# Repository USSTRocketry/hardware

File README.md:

USST Rocketry Avionics hardware

Telemetry board (Infozilla)

SRAD flight computer board (Phoenix)

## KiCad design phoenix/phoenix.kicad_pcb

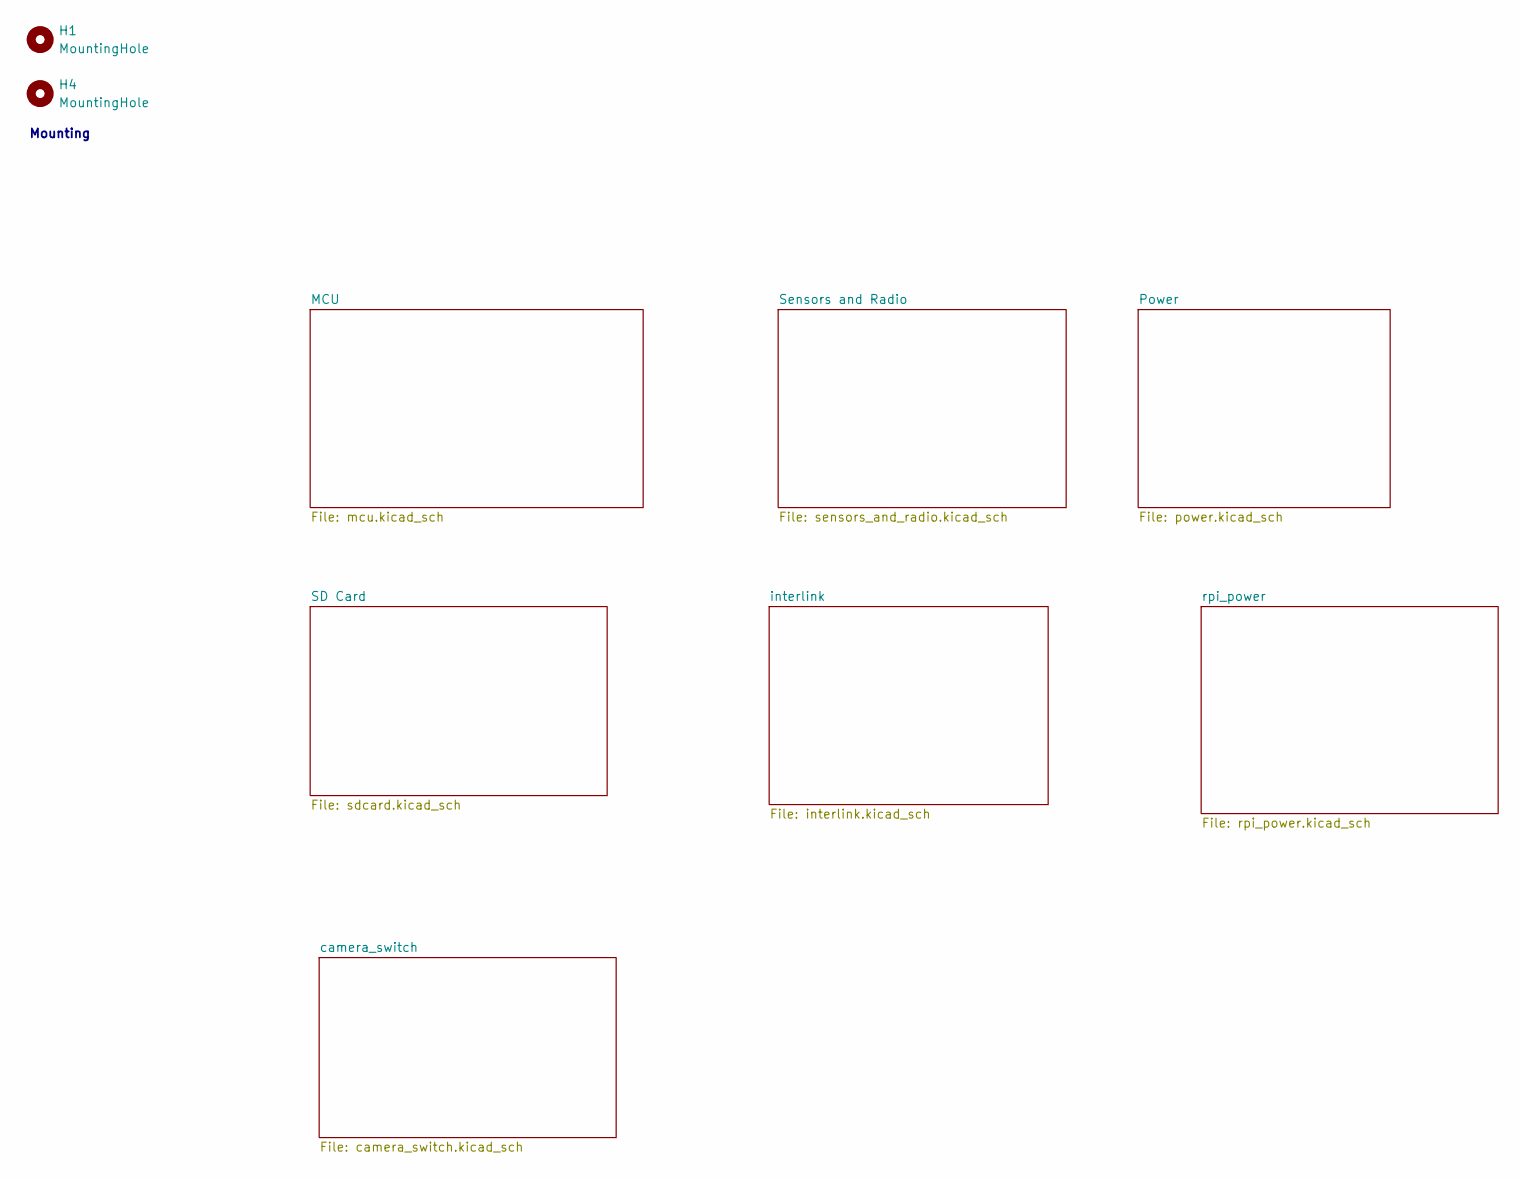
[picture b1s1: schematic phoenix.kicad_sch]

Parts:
H1, H4: MountingHole; MountingHole_3.2mm_M3

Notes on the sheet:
Mounting

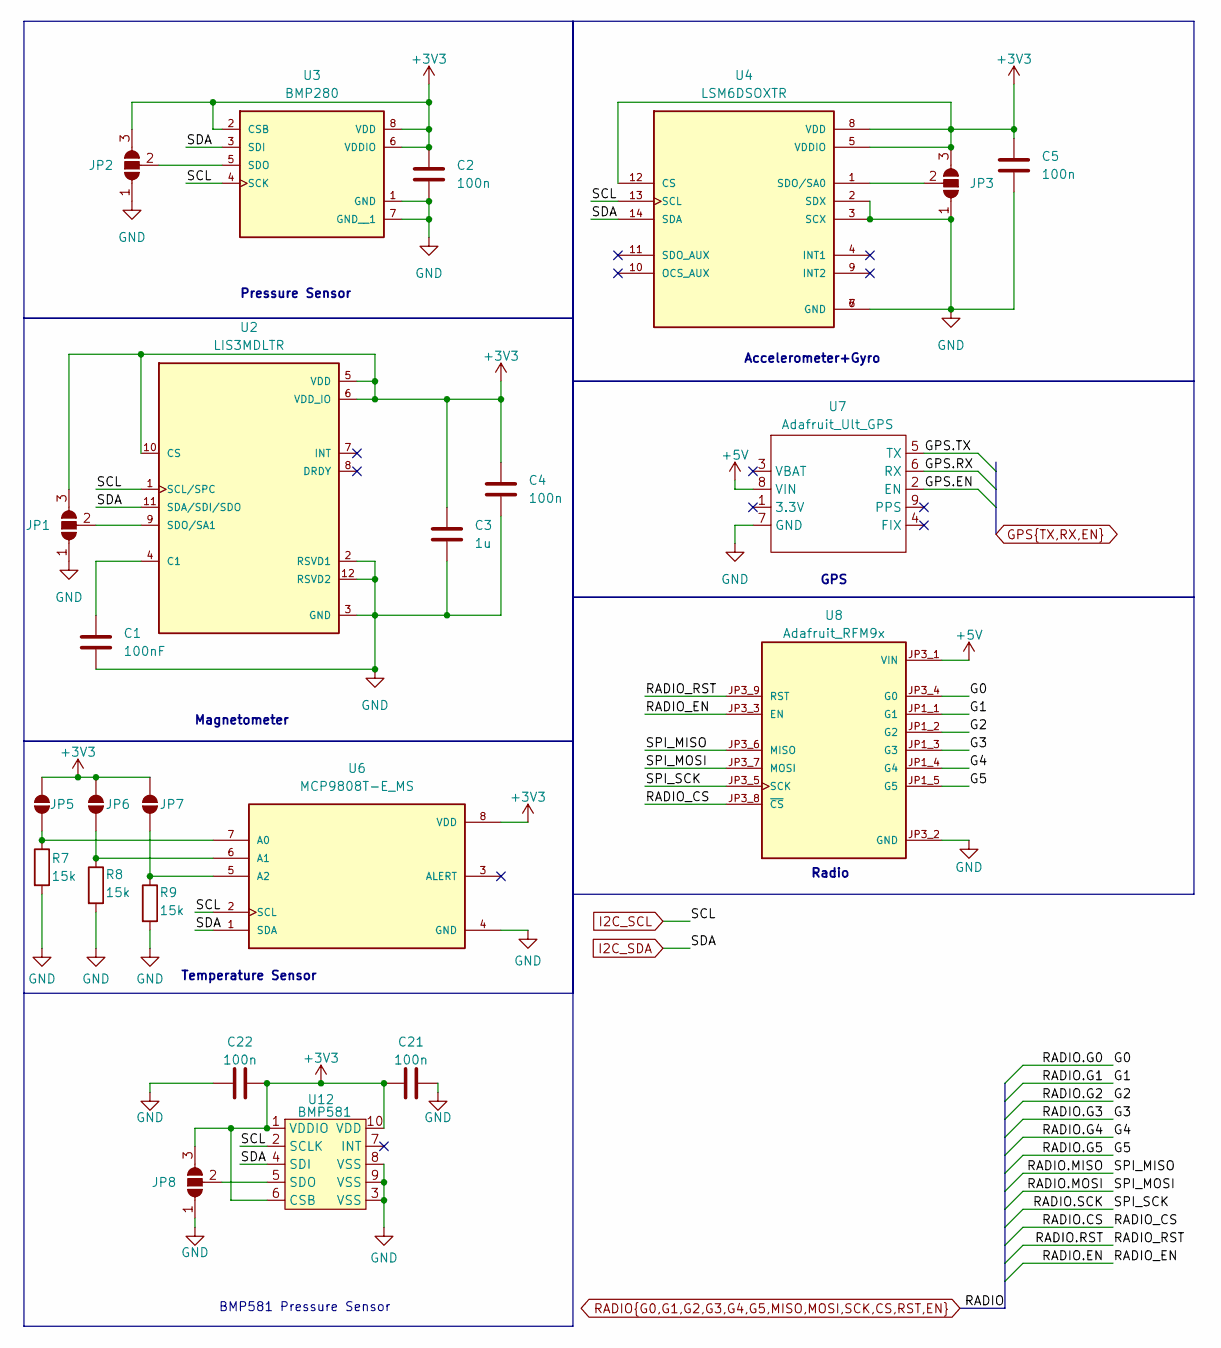
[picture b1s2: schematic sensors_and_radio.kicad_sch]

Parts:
C1: 100nF; C_0603_1608Metric_Pad1.08x0.95mm_HandSolder
C2, C4, C5, C21, C22: 100n; C_0603_1608Metric_Pad1.08x0.95mm_HandSolder
C3: 1u; C_0603_1608Metric_Pad1.08x0.95mm_HandSolder
JP1, JP2, JP3, JP8: SolderJumper_3_Open; SolderJumper-3_P1.3mm_Open_Pad1.0x1.5mm_NumberLabels
JP5, JP6, JP7: SolderJumper_2_Open; SolderJumper-2_P1.3mm_Open_Pad1.0x1.5mm
R7, R8, R9: 15k; R_0603_1608Metric_Pad0.98x0.95mm_HandSolder
U2: LIS3MDLTR; PARTREV 6
U3: BMP280; PART_REV 1.19
U4: LSM6DSOXTR; PARTREV 3.0
U6: MCP9808T-E_MS
U7: Adafruit_Ult_GPS
U8: Adafruit_RFM9x; Adafuit_RFM9x; PARTREV 2023-10-24
U12: BMP581; ST_HLGA-10_2x2mm_P0.5mm_LayoutBorder3x2y

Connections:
+3V3: C2.1, C3.1, C4.1, C5.2, C21.1, C22.2, JP1.3 (B), JP2.3 (B), JP3.3 (B), JP5.2 (B), JP6.2 (B), JP7.2 (B), JP8.3 (B), U2.5 (VDD), U2.6 (VDD_IO), U2.10 (CS), U3.2 (CSB), U3.6 (VDDIO), U3.8 (VDD), U4.5 (VDDIO), U4.8 (VDD), U4.12 (CS), U6.8 (VDD), U12.1 (VDDIO), U12.6 (CSB), U12.10 (VDD); also elsewhere on the board
+5V: U7.8 (VIN), U8.JP3_1 (VIN); also elsewhere on the board
GND: C1.2, C2.2, C3.2, C4.2, C5.1, C21.2, C22.1, JP1.1 (A), JP2.1 (A), JP3.1 (A), JP8.1 (A), R7.2, R8.2, R9.2, U2.2 (RSVD1), U2.3 (GND), U2.12 (RSVD2), U3.1 (GND), U3.7 (GND__1), U4.2 (SDX), U4.3 (SCX), U4.6 (GND), U4.7 (GND), U6.4 (GND), U7.7 (GND), U8.JP3_2 (GND), U12.3 (VSS), U12.8 (VSS), U12.9 (VSS); also elsewhere on the board
GPS.EN: U7.2 (EN); also elsewhere on the board
GPS.RX: U7.6 (RX); also elsewhere on the board
GPS.TX: U7.5 (TX); also elsewhere on the board
I2C_SCL: U2.1 (SCL/SPC), U3.4 (SCK), U4.13 (SCL), U6.2 (SCL), U12.2 (SCLK); also elsewhere on the board
I2C_SDA: U2.11 (SDA/SDI/SDO), U3.3 (SDI), U4.14 (SDA), U6.1 (SDA), U12.4 (SDI); also elsewhere on the board
unnamed: JP1.2 (C), U2.9 (SDO/SA1)
unnamed: JP2.2 (C), U3.5 (SDO)
unnamed: JP3.2 (C), U4.1 (SDO/SA0)
unnamed: JP5.1 (A), R7.1, U6.7 (A0)
unnamed: JP6.1 (A), R8.1, U6.6 (A1)
unnamed: JP7.1 (A), R9.1, U6.5 (A2)
unnamed: JP8.2 (C), U12.5 (SDO)
unnamed: C1.1, U2.4 (C1)
RADIO.CS: U8.JP3_8 (~CS); also elsewhere on the board
RADIO.EN: U8.JP3_3 (EN); also elsewhere on the board
RADIO.G0: U8.JP3_4 (G0); also elsewhere on the board
RADIO.G1: U8.JP1_1 (G1); also elsewhere on the board
RADIO.G2: U8.JP1_2 (G2); also elsewhere on the board
RADIO.G3: U8.JP1_3 (G3); also elsewhere on the board
RADIO.G4: U8.JP1_4 (G4); also elsewhere on the board
RADIO.G5: U8.JP1_5 (G5); also elsewhere on the board
RADIO.MISO: U8.JP3_6 (MISO); also elsewhere on the board
RADIO.MOSI: U8.JP3_7 (MOSI); also elsewhere on the board
RADIO.RST: U8.JP3_9 (RST); also elsewhere on the board
RADIO.SCK: U8.JP3_5 (SCK); also elsewhere on the board

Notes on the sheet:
Radio
Magnetometer
Temperature Sensor
Pressure Sensor
Accelerometer+Gyro
GPS
BMP581 Pressure Sensor

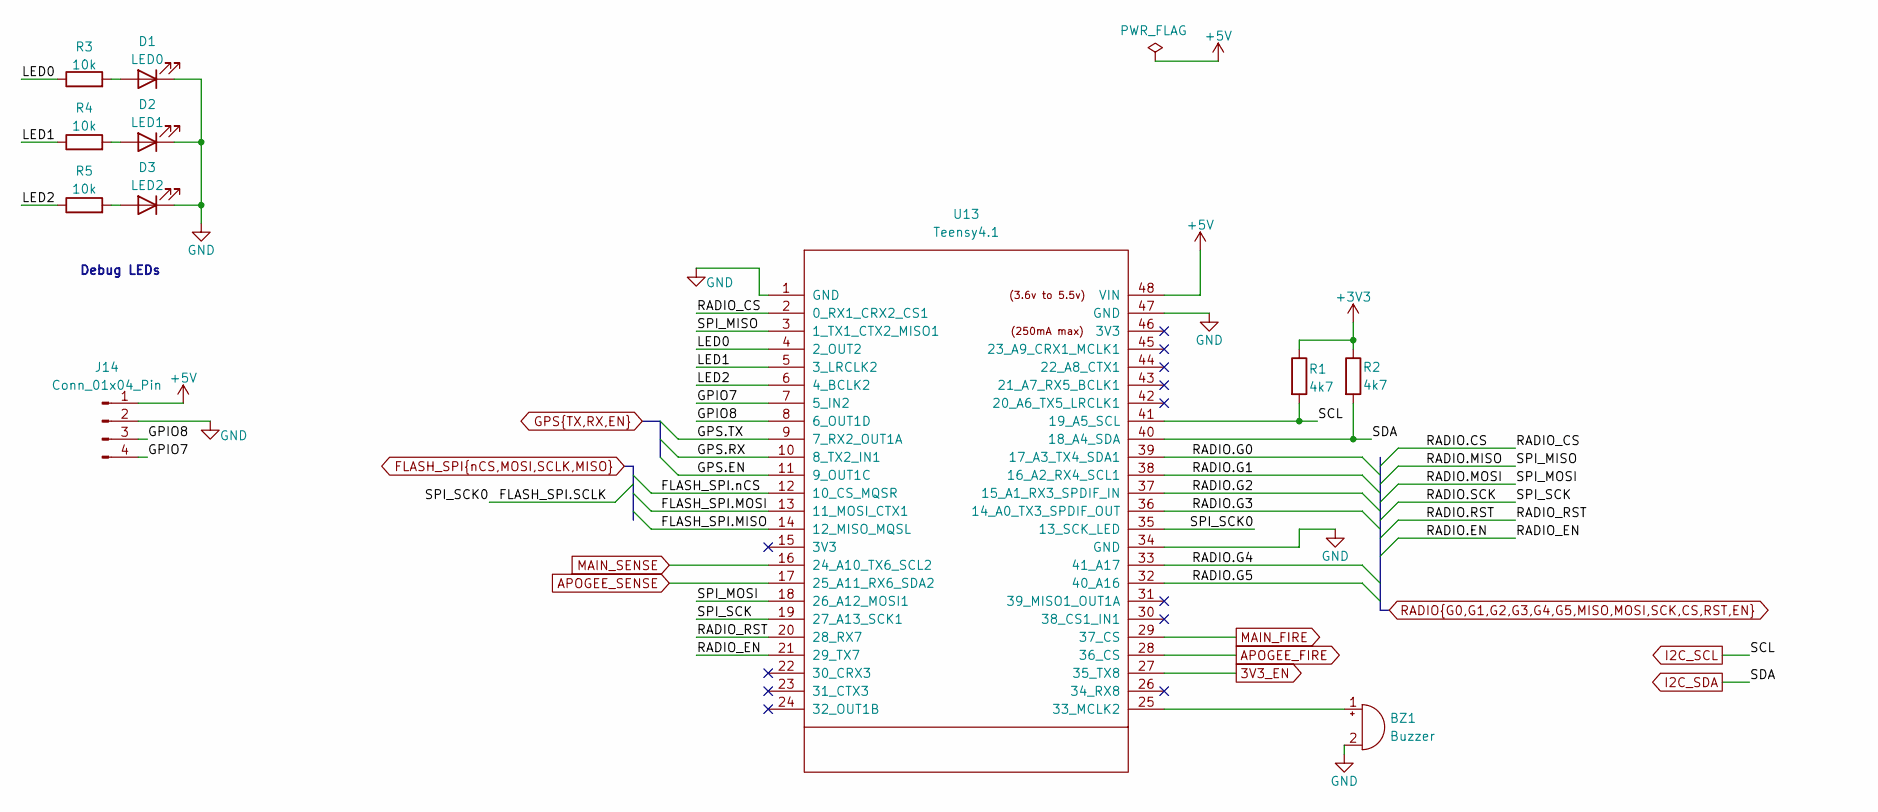
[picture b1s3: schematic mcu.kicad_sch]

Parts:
BZ1: Buzzer; MagneticBuzzer_PUI_AT-0927-TT-6-R
D1: LED0; LED_0603_1608Metric
D2: LED1; LED_0603_1608Metric
D3: LED2; LED_0603_1608Metric
J14: Conn_01x04_Pin; JST_XH_S4B-XH-A_1x04_P2.50mm_Horizontal
R1, R2: 4k7; R_0603_1608Metric_Pad0.98x0.95mm_HandSolder
R3, R4, R5: 10k; R_0603_1608Metric_Pad0.98x0.95mm_HandSolder
U13: Teensy4.1; Teensy41_simplified

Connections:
3V3_EN: U13.27 (35_TX8); also elsewhere on the board
+3V3: R1.1, R2.1; also elsewhere on the board
+5V: J14.1, U13.48 (VIN); also elsewhere on the board
/MCU/GPIO7: J14.4, U13.7 (5_IN2)
/MCU/GPIO8: J14.3, U13.8 (6_OUT1D)
/MCU/LED0: R3.1, U13.4 (2_OUT2)
/MCU/LED1: R4.1, U13.5 (3_LRCLK2)
/MCU/LED2: R5.1, U13.6 (4_BCLK2)
APOGEE_FIRE: U13.28 (36_CS); also elsewhere on the board
APOGEE_SENSE: U13.17 (25_A11_RX6_SDA2); also elsewhere on the board
FLASH_SPI.MISO: U13.14 (12_MISO_MQSL); also elsewhere on the board
FLASH_SPI.MOSI: U13.13 (11_MOSI_CTX1); also elsewhere on the board
FLASH_SPI.SCLK: U13.35 (13_SCK_LED); also elsewhere on the board
FLASH_SPI.nCS: U13.12 (10_CS_MQSR); also elsewhere on the board
GND: BZ1.2 (-), D1.1 (K), D2.1 (K), D3.1 (K), J14.2, U13.1 (GND), U13.34 (GND), U13.47 (GND); also elsewhere on the board
GPS.EN: U13.11 (9_OUT1C); also elsewhere on the board
GPS.RX: U13.10 (8_TX2_IN1); also elsewhere on the board
GPS.TX: U13.9 (7_RX2_OUT1A); also elsewhere on the board
I2C_SCL: R1.2, U13.41 (19_A5_SCL); also elsewhere on the board
I2C_SDA: R2.2, U13.40 (18_A4_SDA); also elsewhere on the board
MAIN_FIRE: U13.29 (37_CS); also elsewhere on the board
MAIN_SENSE: U13.16 (24_A10_TX6_SCL2); also elsewhere on the board
unnamed: BZ1.1 (+), U13.25 (33_MCLK2)
unnamed: D1.2 (A), R3.2
unnamed: D2.2 (A), R4.2
unnamed: D3.2 (A), R5.2
RADIO.CS: U13.2 (0_RX1_CRX2_CS1); also elsewhere on the board
RADIO.EN: U13.21 (29_TX7); also elsewhere on the board
RADIO.G0: U13.39 (17_A3_TX4_SDA1); also elsewhere on the board
RADIO.G1: U13.38 (16_A2_RX4_SCL1); also elsewhere on the board
RADIO.G2: U13.37 (15_A1_RX3_SPDIF_IN); also elsewhere on the board
RADIO.G3: U13.36 (14_A0_TX3_SPDIF_OUT); also elsewhere on the board
RADIO.G4: U13.33 (41_A17); also elsewhere on the board
RADIO.G5: U13.32 (40_A16); also elsewhere on the board
RADIO.MISO: U13.3 (1_TX1_CTX2_MISO1); also elsewhere on the board
RADIO.MOSI: U13.18 (26_A12_MOSI1); also elsewhere on the board
RADIO.RST: U13.20 (28_RX7); also elsewhere on the board
RADIO.SCK: U13.19 (27_A13_SCK1); also elsewhere on the board

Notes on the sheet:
Debug LEDs

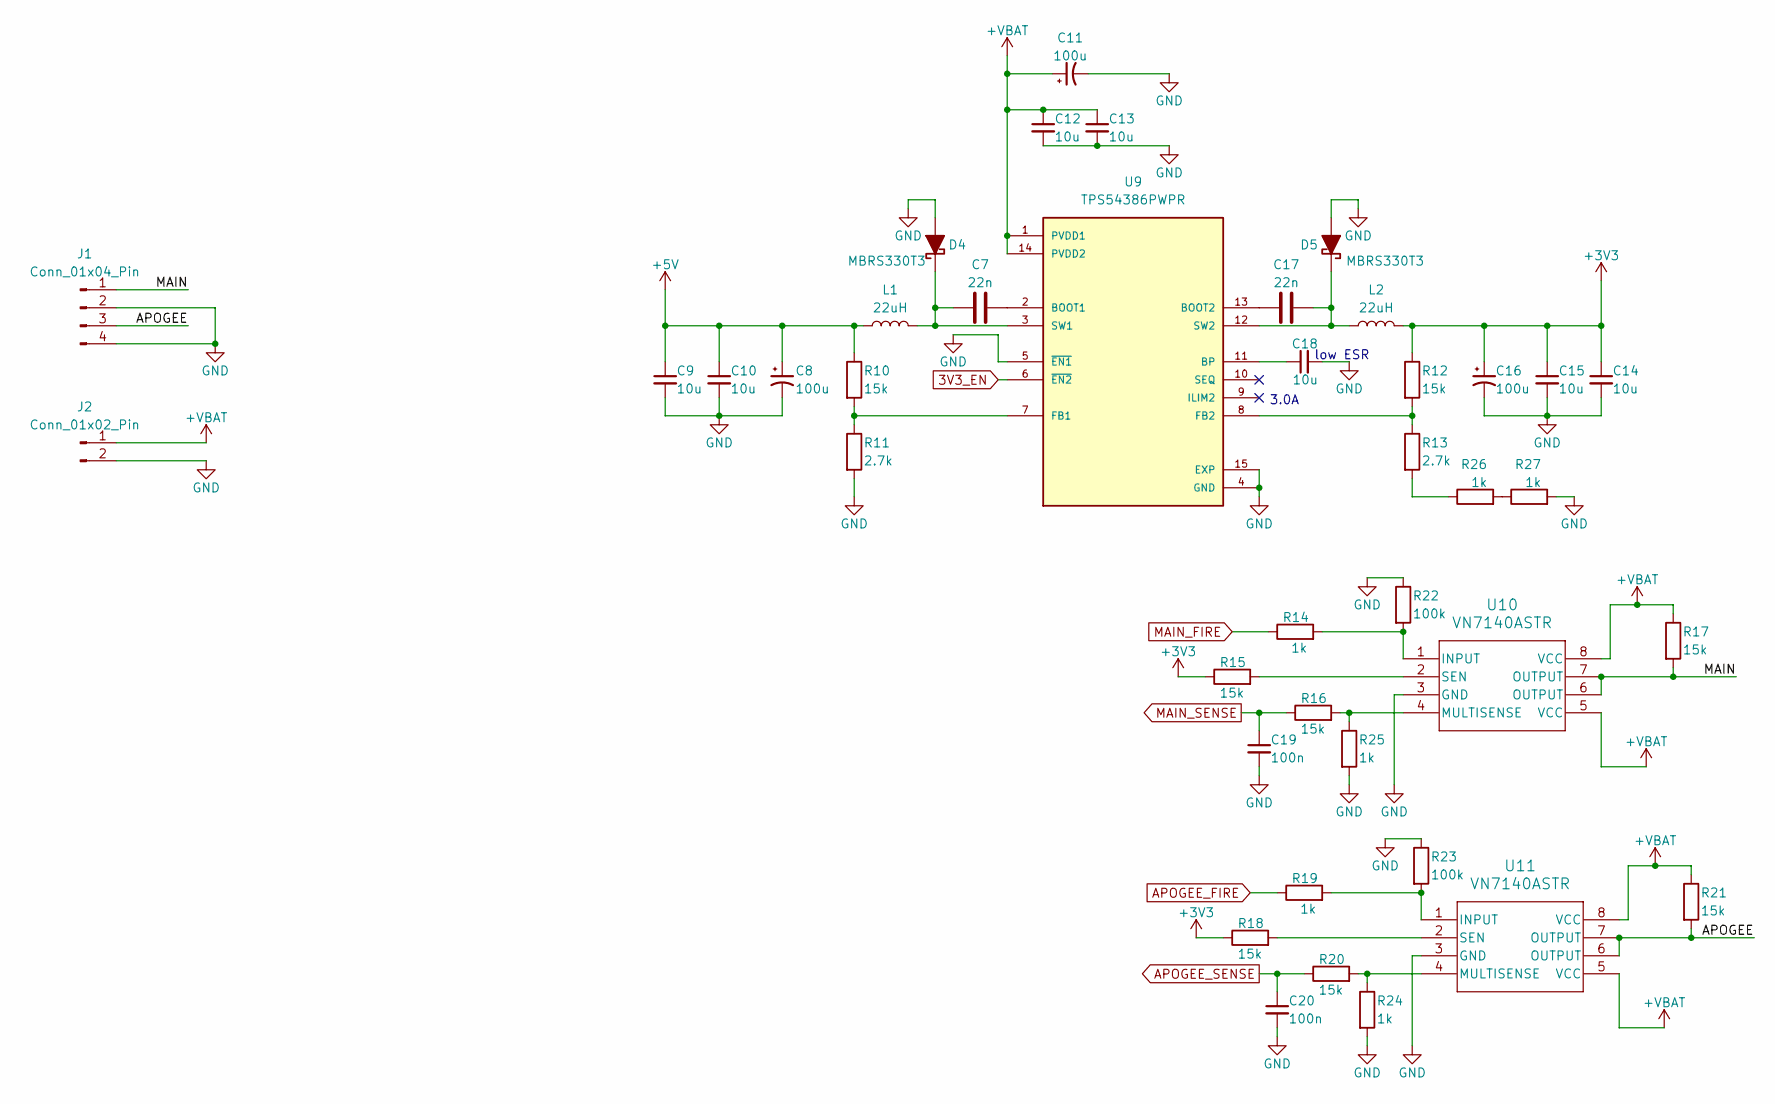
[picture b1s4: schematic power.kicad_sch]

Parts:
C7, C17: 22n; C_0603_1608Metric_Pad1.08x0.95mm_HandSolder
C8, C11, C16: 100u; C_0603_1608Metric_Pad1.08x0.95mm_HandSolder
C9, C10, C12, C13, C14, C15, C18: 10u; C_0603_1608Metric_Pad1.08x0.95mm_HandSolder
C19, C20: 100n; C_0603_1608Metric_Pad1.08x0.95mm_HandSolder
D4, D5: MBRS330T3; D_SMB_Handsoldering
J1: Conn_01x04_Pin; JST_XH_S4B-XH-A_1x04_P2.50mm_Horizontal
J2: Conn_01x02_Pin; JST_XH_S2B-XH-A_1x02_P2.50mm_Horizontal
L1, L2: 22uH; L_AMDLH5030S
R10, R12, R15, R16, R17, R18, R20, R21: 15k; R_0603_1608Metric_Pad0.98x0.95mm_HandSolder
R11, R13: 2.7k; R_0603_1608Metric_Pad0.98x0.95mm_HandSolder
R14, R19, R24, R25, R26, R27: 1k; R_0603_1608Metric_Pad0.98x0.95mm_HandSolder
R22, R23: 100k; R_0603_1608Metric_Pad0.98x0.95mm_HandSolder
U9: TPS54386PWPR; IC_TPS54386PWPR; PARTREV C
U10, U11: VN7140ASTR; VN7140ASTR_SO-8

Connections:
3V3_EN: U9.6 (~EN2); also elsewhere on the board
+3V3: C14.1, C15.1, C16.1, L2.1, R12.1, R15.1, R18.1; also elsewhere on the board
+5V: C8.1, C9.1, C10.1, L1.1, R10.1; also elsewhere on the board
+VBAT: C11.1, C12.1, C13.1, J2.1, R17.1, R21.1, U9.1 (PVDD1), U9.14 (PVDD2), U10.5 (VCC), U10.8 (VCC), U11.5 (VCC), U11.8 (VCC)
/Power/APOGEE: J1.3, R21.2, U11.6 (OUTPUT), U11.7 (OUTPUT)
/Power/MAIN: J1.1, R17.2, U10.6 (OUTPUT), U10.7 (OUTPUT)
APOGEE_FIRE: R19.1; also elsewhere on the board
APOGEE_SENSE: C20.1, R20.1; also elsewhere on the board
GND: C8.2, C9.2, C10.2, C11.2, C12.2, C13.2, C14.2, C15.2, C16.2, C18.2, C19.2, C20.2, D4.2 (A), D5.2 (A), J1.2, J1.4, J2.2, R11.2, R22.1, R23.1, R24.2, R25.2, R27.2, U9.4 (GND), U9.5 (~EN1), U9.15 (EXP), U10.3 (GND), U11.3 (GND); also elsewhere on the board
MAIN_FIRE: R14.1; also elsewhere on the board
MAIN_SENSE: C19.1, R16.1; also elsewhere on the board
unnamed: C7.1, D4.1 (K), L1.2, U9.3 (SW1)
unnamed: C17.1, D5.1 (K), L2.2, U9.12 (SW2)
unnamed: R13.2, R26.1
unnamed: R26.2, R27.1
unnamed: C7.2, U9.2 (BOOT1)
unnamed: C17.2, U9.13 (BOOT2)
unnamed: C18.1, U9.11 (BP)
unnamed: R10.2, R11.1, U9.7 (FB1)
unnamed: R12.2, R13.1, U9.8 (FB2)
unnamed: R14.2, R22.2, U10.1 (INPUT)
unnamed: R16.2, R25.1, U10.4 (MULTISENSE)
unnamed: R15.2, U10.2 (SEN)
unnamed: R19.2, R23.2, U11.1 (INPUT)
unnamed: R20.2, R24.1, U11.4 (MULTISENSE)
unnamed: R18.2, U11.2 (SEN)

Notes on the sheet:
3.0A
low ESR

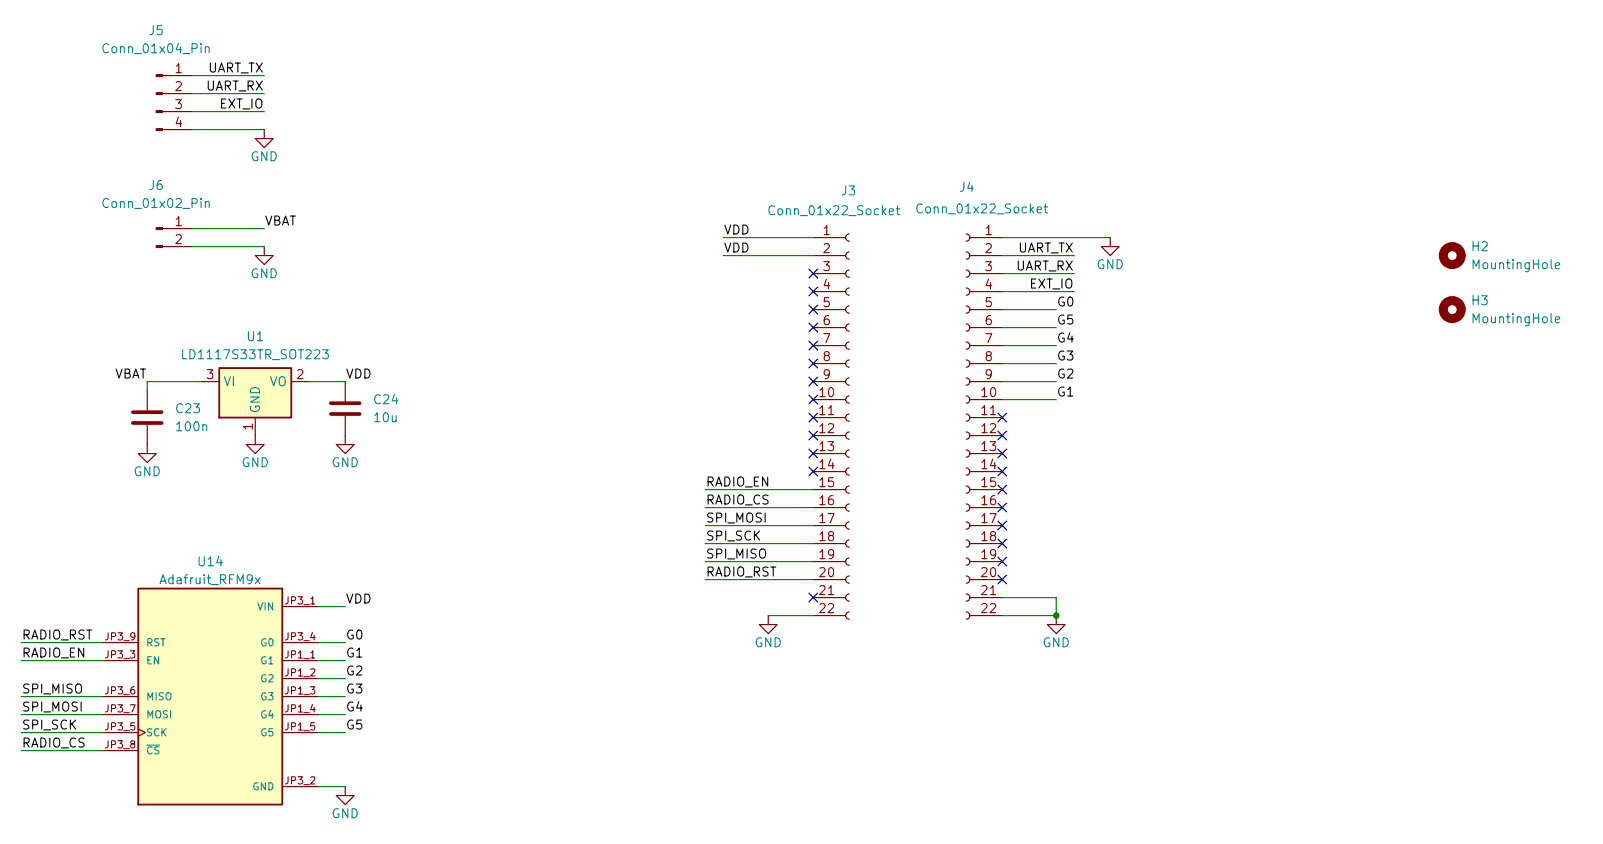
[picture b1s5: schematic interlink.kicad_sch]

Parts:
C23: 100n; C_0603_1608Metric_Pad1.08x0.95mm_HandSolder
C24: 10u; C_0603_1608Metric_Pad1.08x0.95mm_HandSolder
H2, H3: MountingHole; MountingHole_3.2mm_M3
J3, J4: Conn_01x22_Socket; PinHeader_1x22_P2.54mm_Vertical
J5: Conn_01x04_Pin; JST_XH_S4B-XH-A_1x04_P2.50mm_Horizontal
J6: Conn_01x02_Pin; JST_XH_S2B-XH-A_1x02_P2.50mm_Horizontal
U1: LD1117S33TR_SOT223; SOT-223-3_TabPin2
U14: Adafruit_RFM9x; Adafuit_RFM9x; PARTREV 2023-10-24

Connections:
/interlink/EXT_IO: J4.4, J5.3
/interlink/G0: J4.5, U14.JP3_4 (G0)
/interlink/G1: J4.10, U14.JP1_1 (G1)
/interlink/G2: J4.9, U14.JP1_2 (G2)
/interlink/G3: J4.8, U14.JP1_3 (G3)
/interlink/G4: J4.7, U14.JP1_4 (G4)
/interlink/G5: J4.6, U14.JP1_5 (G5)
/interlink/RADIO_CS: J3.16, U14.JP3_8 (~CS)
/interlink/RADIO_EN: J3.15, U14.JP3_3 (EN)
/interlink/RADIO_RST: J3.20, U14.JP3_9 (RST)
/interlink/SPI_MISO: J3.19, U14.JP3_6 (MISO)
/interlink/SPI_MOSI: J3.17, U14.JP3_7 (MOSI)
/interlink/SPI_SCK: J3.18, U14.JP3_5 (SCK)
/interlink/UART_RX: J4.3, J5.2
/interlink/UART_TX: J4.2, J5.1
/interlink/VBAT: C23.2, J6.1, U1.3 (VI)
/interlink/VDD: C24.2, J3.1, J3.2, U1.2 (VO), U14.JP3_1 (VIN)
GND: C23.1, C24.1, J3.22, J4.1, J4.21, J4.22, J5.4, J6.2, U1.1 (GND), U14.JP3_2 (GND); also elsewhere on the board

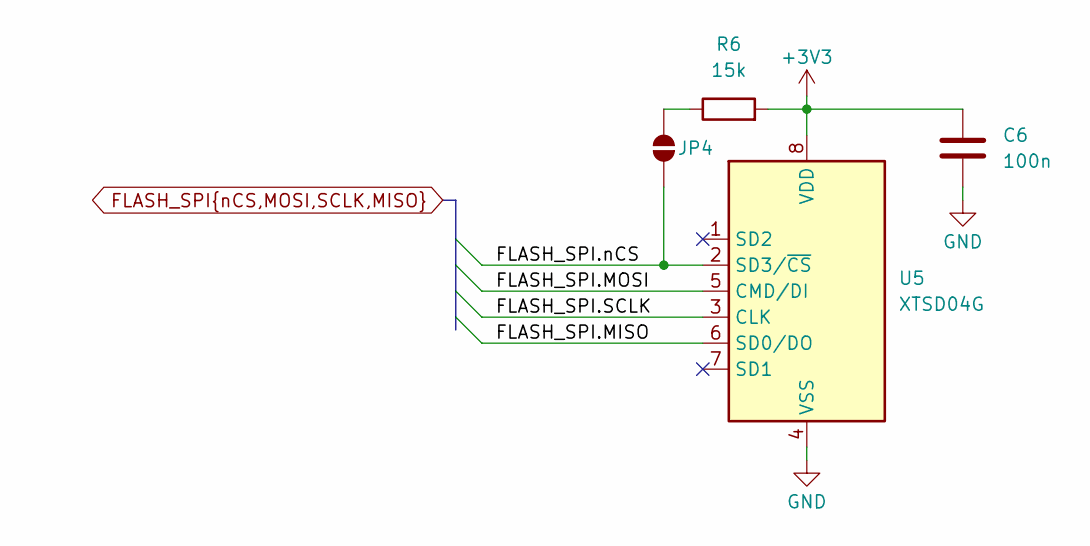
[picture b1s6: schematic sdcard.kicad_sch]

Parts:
C6: 100n; C_0603_1608Metric_Pad1.08x0.95mm_HandSolder
JP4: SD_nCS_Pull_Up; SolderJumper-2_P1.3mm_Open_Pad1.0x1.5mm
R6: 15k; R_0603_1608Metric_Pad0.98x0.95mm_HandSolder
U5: XTSD04G; LGA-8_8x6mm_P1.27mm

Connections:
+3V3: C6.1, R6.2, U5.8 (VDD); also elsewhere on the board
FLASH_SPI.MISO: U5.6 (SD0/DO); also elsewhere on the board
FLASH_SPI.MOSI: U5.5 (CMD/DI); also elsewhere on the board
FLASH_SPI.SCLK: U5.3 (CLK); also elsewhere on the board
FLASH_SPI.nCS: JP4.1 (A), U5.2 (SD3/~CS); also elsewhere on the board
GND: C6.2, U5.4 (VSS); also elsewhere on the board
unnamed: JP4.2 (B), R6.1

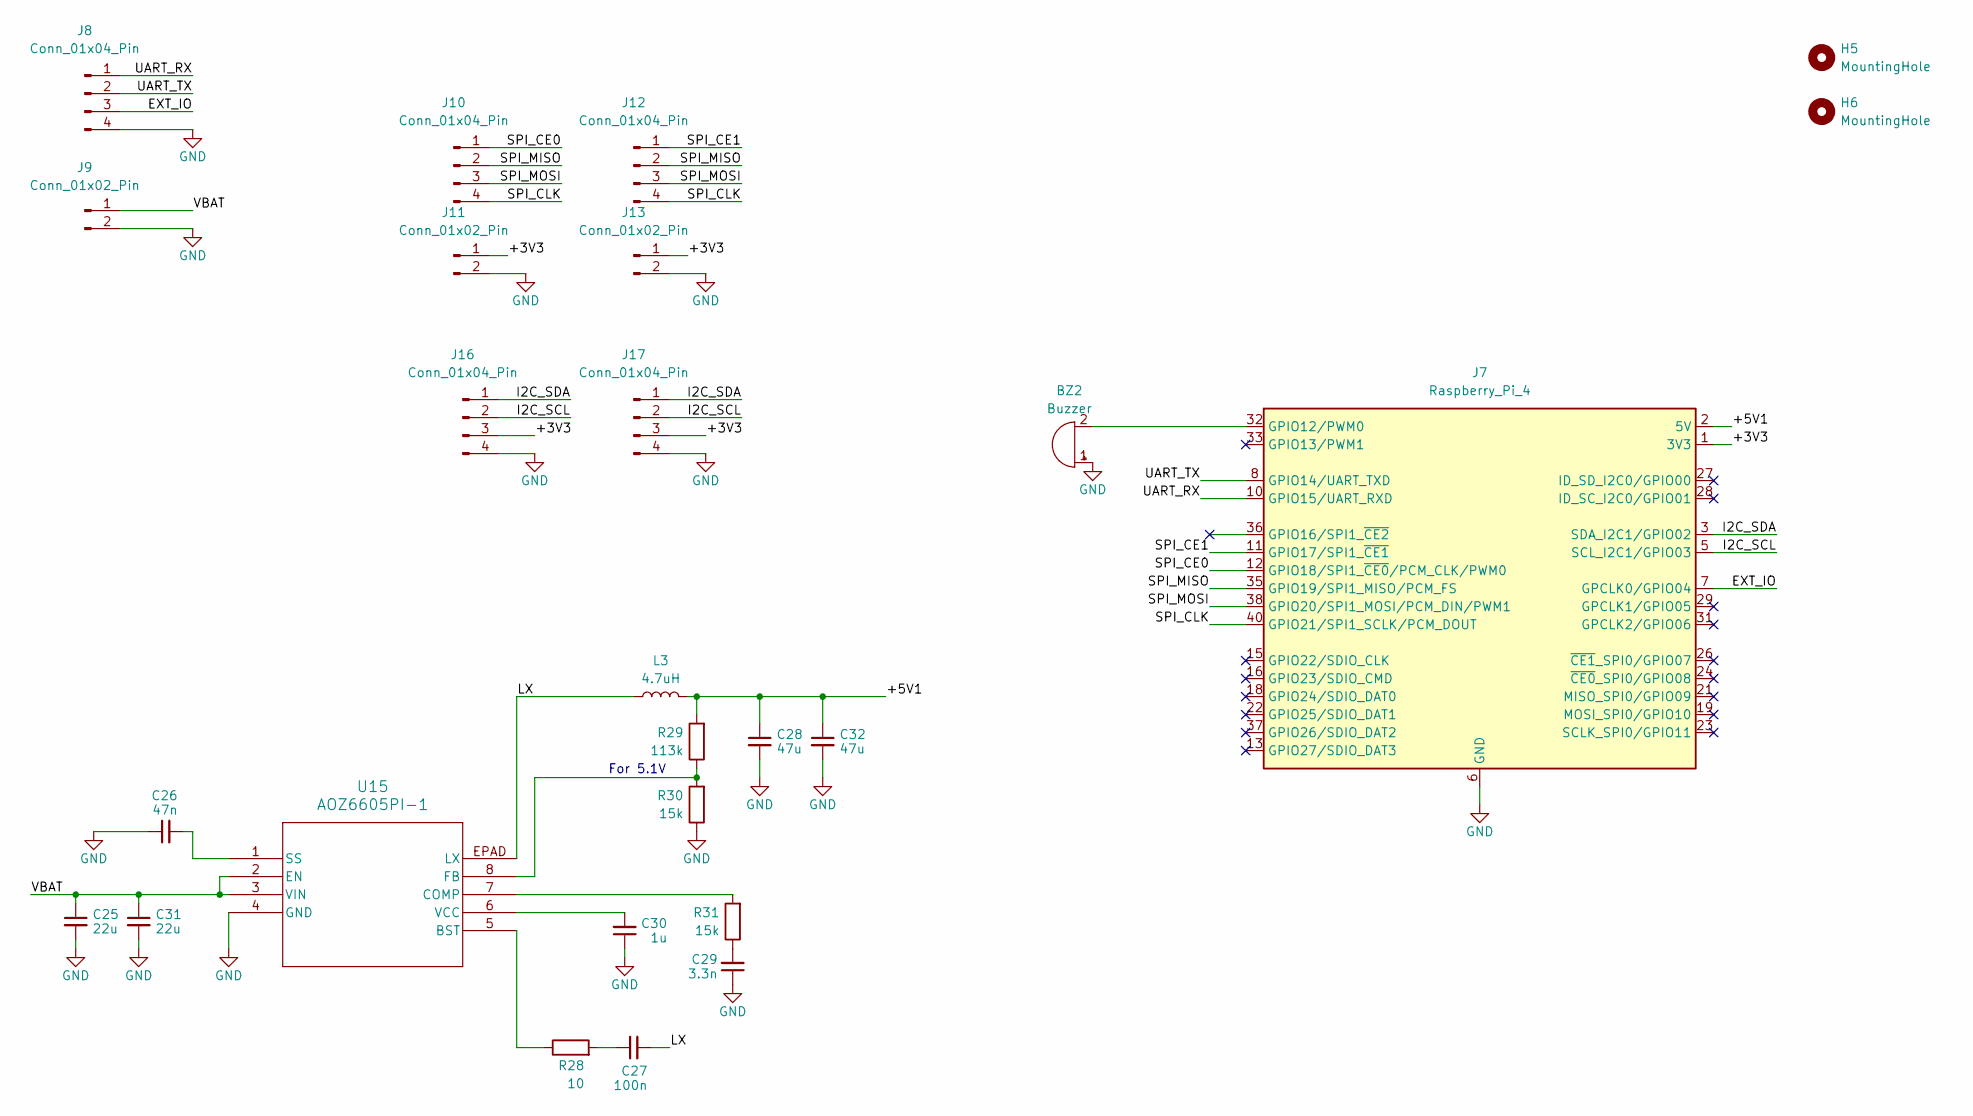
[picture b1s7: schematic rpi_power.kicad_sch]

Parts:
BZ2: Buzzer; MagneticBuzzer_PUI_AT-0927-TT-6-R
C25, C31: 22u; C_0603_1608Metric_Pad1.08x0.95mm_HandSolder
C26: 47n; C_0603_1608Metric_Pad1.08x0.95mm_HandSolder
C27: 100n; C_0603_1608Metric_Pad1.08x0.95mm_HandSolder
C28, C32: 47u; C_0603_1608Metric_Pad1.08x0.95mm_HandSolder
C29: 3.3n; C_0603_1608Metric_Pad1.08x0.95mm_HandSolder
C30: 1u; C_0603_1608Metric_Pad1.08x0.95mm_HandSolder
H5, H6: MountingHole; MountingHole_3.2mm_M3
J7: Raspberry_Pi_4; PinHeader_2x20_P2.54mm_Vertical
J8, J10, J12, J16, J17: Conn_01x04_Pin; JST_XH_S4B-XH-A_1x04_P2.50mm_Horizontal
J9, J11, J13: Conn_01x02_Pin; JST_XH_S2B-XH-A_1x02_P2.50mm_Horizontal
L3: 4.7uH; L_0603_1608Metric
R28: 10; R_0603_1608Metric_Pad0.98x0.95mm_HandSolder
R29: 113k; R_0603_1608Metric_Pad0.98x0.95mm_HandSolder
R30, R31: 15k; R_0603_1608Metric_Pad0.98x0.95mm_HandSolder
U15: AOZ6605PI-1; SO8_EP1_AOS

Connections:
/rpi_power/+3V3: J7.1 (3V3), J7.17 (3V3), J11.1, J13.1, J16.3, J17.3
/rpi_power/+5V1: C28.1, C32.1, J7.2 (5V), J7.4 (5V), L3.2, R29.2
/rpi_power/EXT_IO: J7.7 (GPCLK0/GPIO04), J8.3
/rpi_power/I2C_SCL: J7.5 (SCL_I2C1/GPIO03), J16.2, J17.2
/rpi_power/I2C_SDA: J7.3 (SDA_I2C1/GPIO02), J16.1, J17.1
/rpi_power/LX: C27.2, L3.1, U15.EPAD (LX)
/rpi_power/SPI_CE0: J7.12 (GPIO18/SPI1_~CE0/PCM_CLK/PWM0), J10.1
/rpi_power/SPI_CE1: J7.11 (GPIO17/SPI1_~CE1), J12.1
/rpi_power/SPI_CLK: J7.40 (GPIO21/SPI1_SCLK/PCM_DOUT), J10.4, J12.4
/rpi_power/SPI_MISO: J7.35 (GPIO19/SPI1_MISO/PCM_FS), J10.2, J12.2
/rpi_power/SPI_MOSI: J7.38 (GPIO20/SPI1_MOSI/PCM_DIN/PWM1), J10.3, J12.3
/rpi_power/UART_RX: J7.10 (GPIO15/UART_RXD), J8.1
/rpi_power/UART_TX: J7.8 (GPIO14/UART_TXD), J8.2
/rpi_power/VBAT: C25.1, C31.1, J9.1, U15.2 (EN), U15.3 (VIN)
GND: BZ2.1 (+), C25.2, C26.1, C28.2, C29.1, C30.1, C31.2, C32.2, J7.6 (GND), J7.9 (GND), J7.14 (GND), J7.20 (GND), J7.25 (GND), J7.30 (GND), J7.34 (GND), J7.39 (GND), J8.4, J9.2, J11.2, J13.2, J16.4, J17.4, R30.1, U15.4 (GND); also elsewhere on the board
unnamed: BZ2.2 (-), J7.32 (GPIO12/PWM0)
unnamed: C27.1, R28.2
unnamed: C29.2, R31.1
unnamed: R28.1, U15.5 (BST)
unnamed: R31.2, U15.7 (COMP)
unnamed: R29.1, R30.2, U15.8 (FB)
unnamed: C26.2, U15.1 (SS)
unnamed: C30.2, U15.6 (VCC)

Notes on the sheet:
For 5.1V

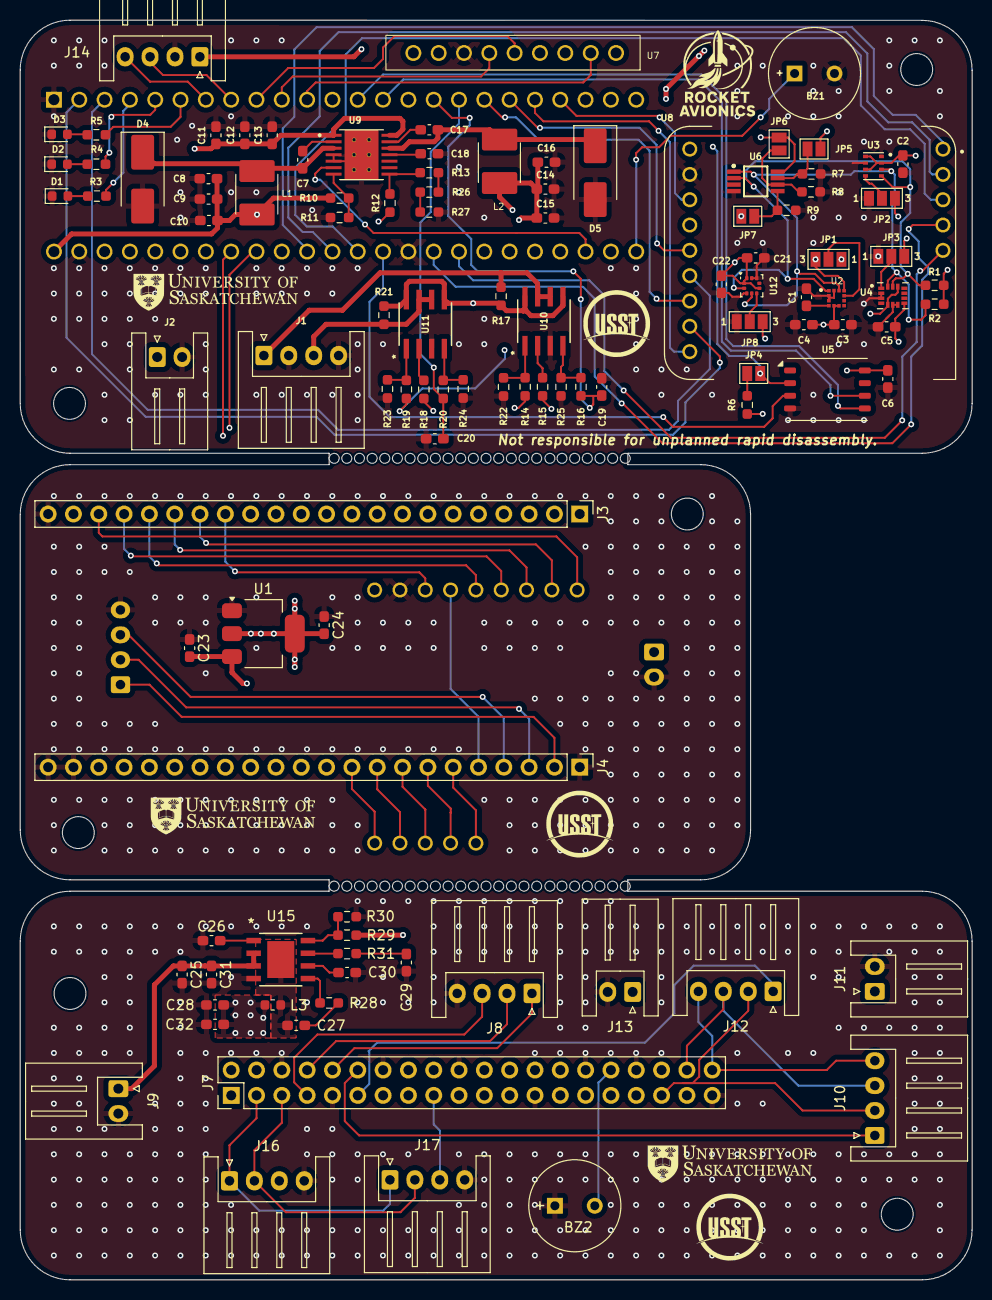
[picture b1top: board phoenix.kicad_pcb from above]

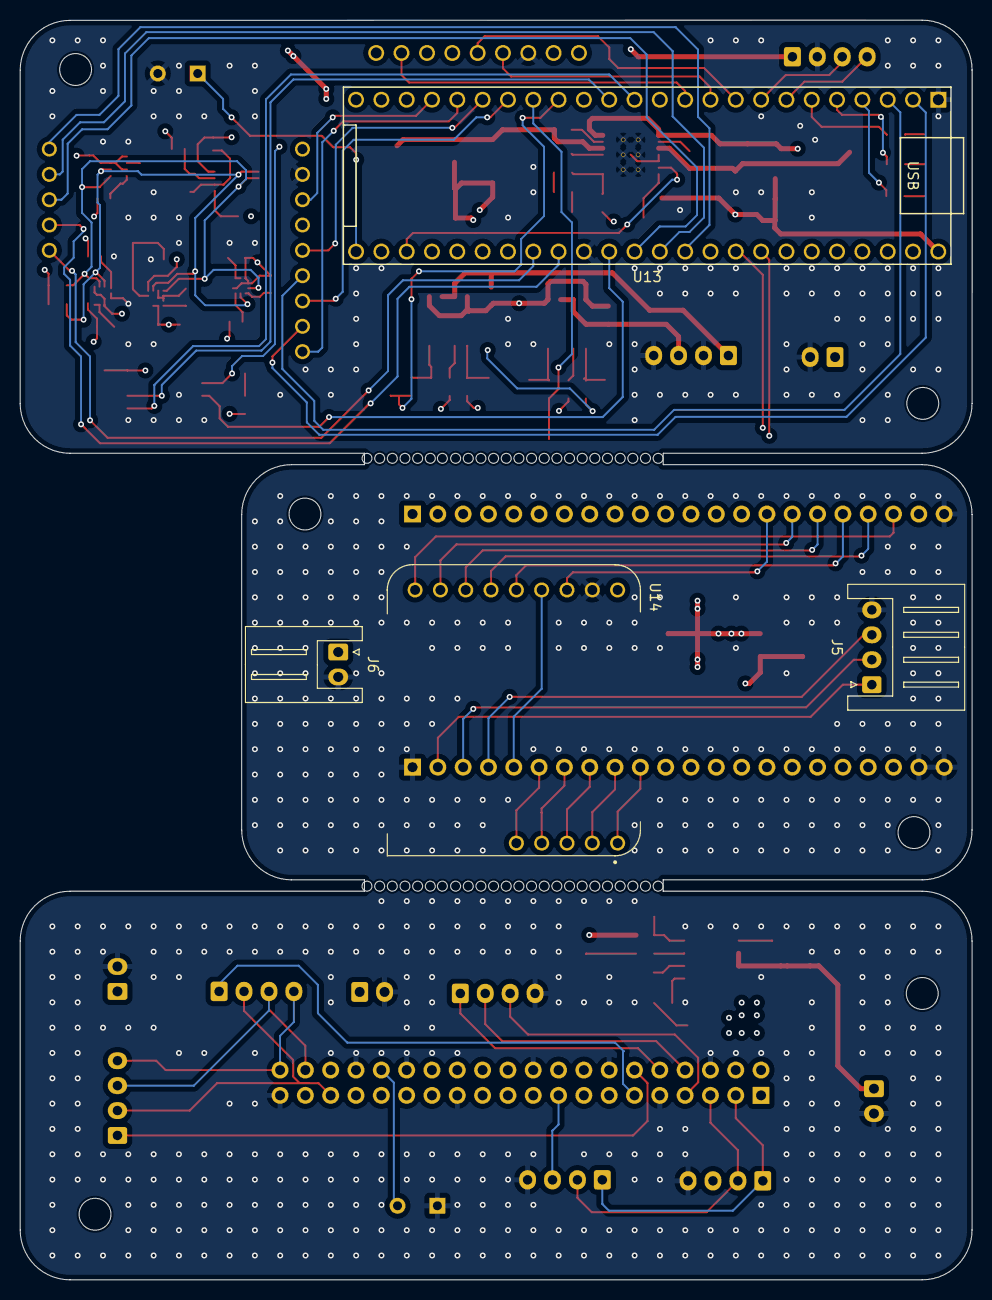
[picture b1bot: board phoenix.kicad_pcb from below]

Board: 4 copper layers, 95.5 x 126.4 mm, 118 parts (4 on the bottom side), 104 nets.

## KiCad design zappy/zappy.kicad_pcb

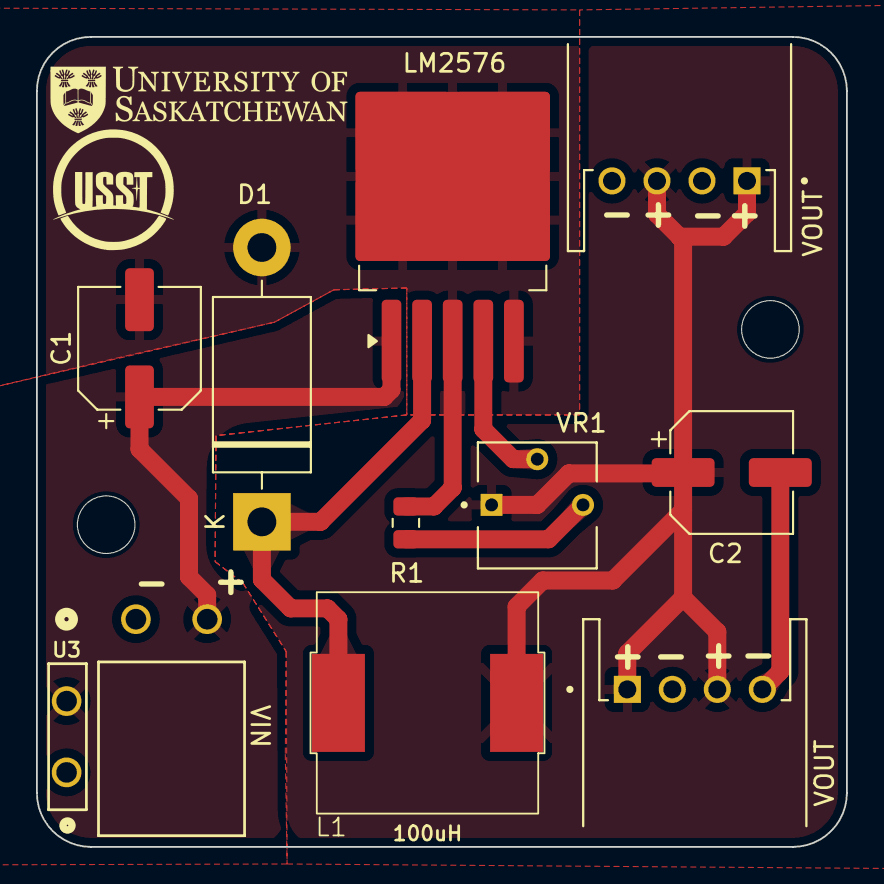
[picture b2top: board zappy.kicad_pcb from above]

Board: 2 copper layers, 45.0 x 45.0 mm, 13 parts (0 on the bottom side), 6 nets.

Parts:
C1: 100uF; CP_Elec_6.3x7.7
C2: 330uF; CP_Elec_6.3x7.7
D1: 1N5822; D_DO-201AD_P15.24mm_Horizontal
H1, H2: MountingHole; MountingHole_3.2mm_M3
L1: 100uH; SMDRI127-101MT
LM2576: LM2576T-ADJ; TO-263-5_TabPin3
R1: 3k8; R_0805_2012Metric
U3: S2P-VH; S2P-VH_JST_Only_holes
VIN: S2P-VH; S2P-VH_JST
VOUT: JST_S4B-XH-A-1
VOUT#2: JST_S4B-XH-A-1
VR1: TRIM_3362P_10k_VR; TRIM_3362P-1-103LF

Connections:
/Vin: C1.1, LM2576.1 (VIN), U3.2, VIN.2
/Vout: C2.1, L1.2, VOUT.1, VOUT.3, VOUT#2.1, VOUT#2.3, VR1.1
GND: C1.2, C2.2, D1.2 (A), LM2576.3 (GND), LM2576.5 (~ON/OFF), R1.2, U3.1, VIN.1, VOUT.2, VOUT.4, VOUT#2.2, VOUT#2.4
unnamed: D1.1 (K), L1.1, LM2576.2 (OUT)
unnamed: R1.1, VR1.3
unnamed: LM2576.4 (FB), VR1.2
